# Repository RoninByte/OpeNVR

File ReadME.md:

BOARD STATUS: In Production

Photo's of the PCB;

Features:

M-Key M.2 PCIe Gen 3 X2 Slot

E-Key M.2 PCIe Gen 3 X1 Slot

2x 2.5GBe Ethernet Ports (Realtek's RTL8125BG-CG)

4x Molex Mini-Fit Jr for powering upto 3.5" Sata drives

5v Fan header for the built in fan on the Lattepanda MU

12v Fan Header for a system fan

HDMI 2.1

2x USB 3.2 Gen 2

2x USB 2.0

DDR4 SO-DIMM Slot for Lattepanda MU (Many options to choose from)

Uses Nano-ITX Standard

20v USB-C PD Input.

Dual Bios to switch between MU Bios and Your own Custom Bios

6x Sata Ports (ASM1166)

* 2 Sata ports will remain unpopulated however they will be connected to the IC incase you want to add more ports

Sata Ports LED (Once again optional)

Any Suggestions Just Open an Issue and i'll take a look

Credits:

EShark 

WifiCable for improvements and fixes

Lattepanda Team For Lattepanda MU Lite Kit

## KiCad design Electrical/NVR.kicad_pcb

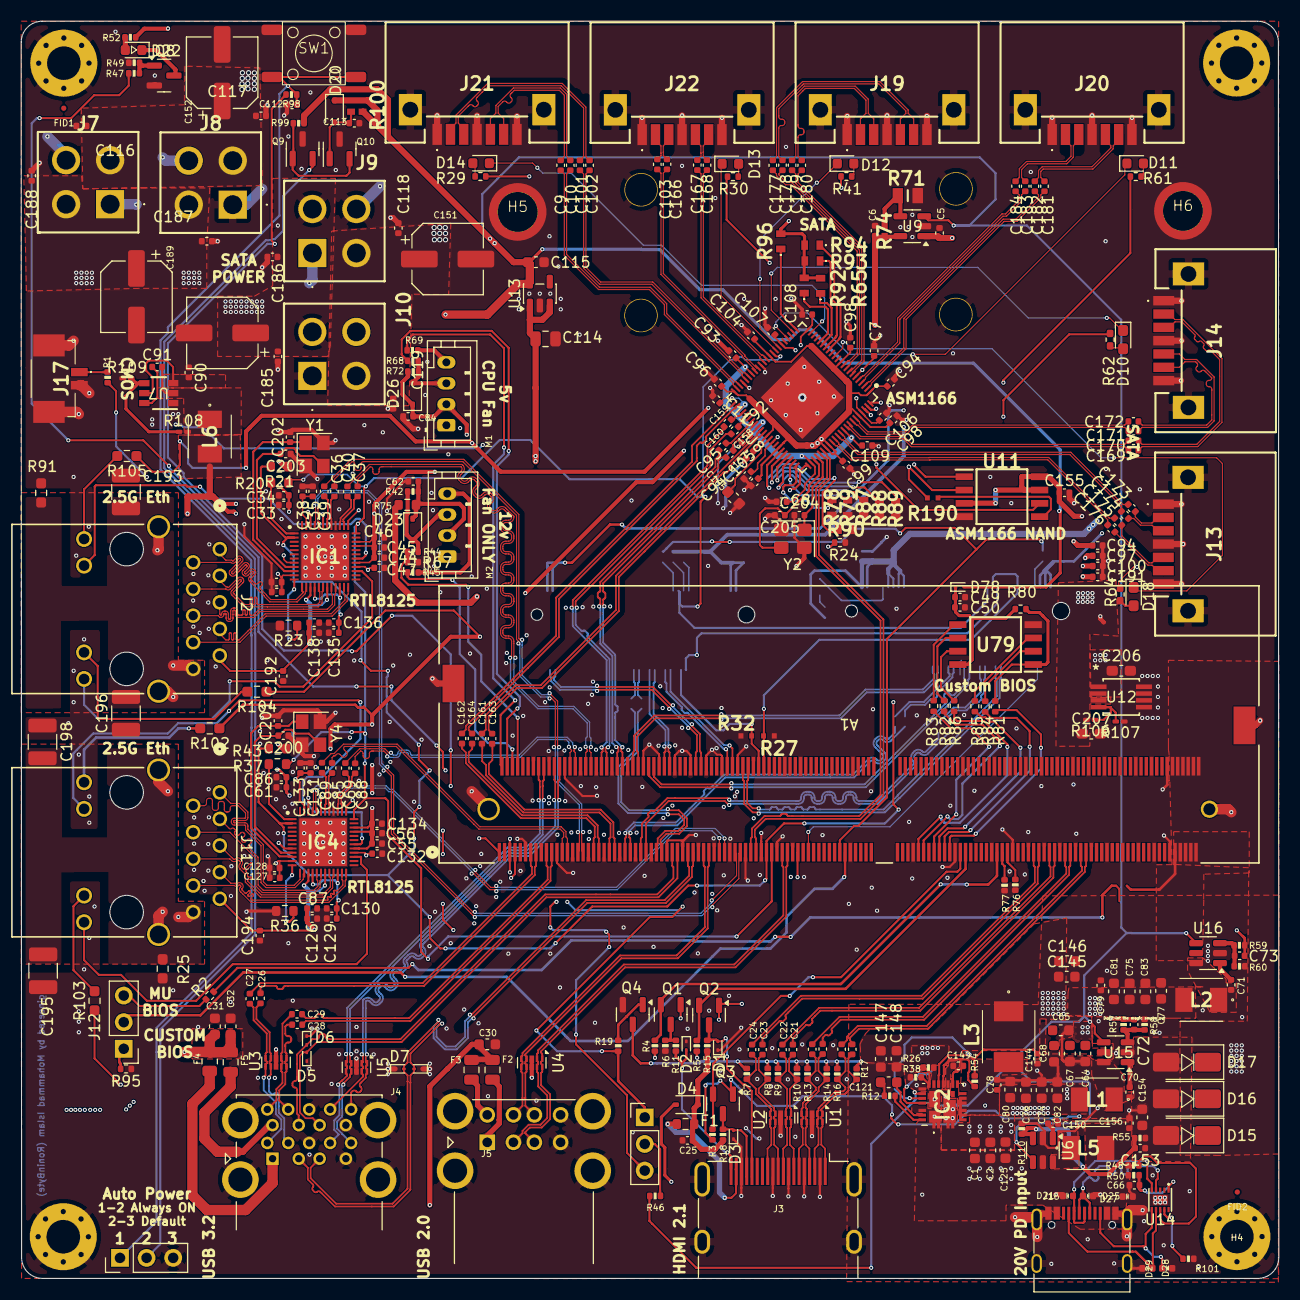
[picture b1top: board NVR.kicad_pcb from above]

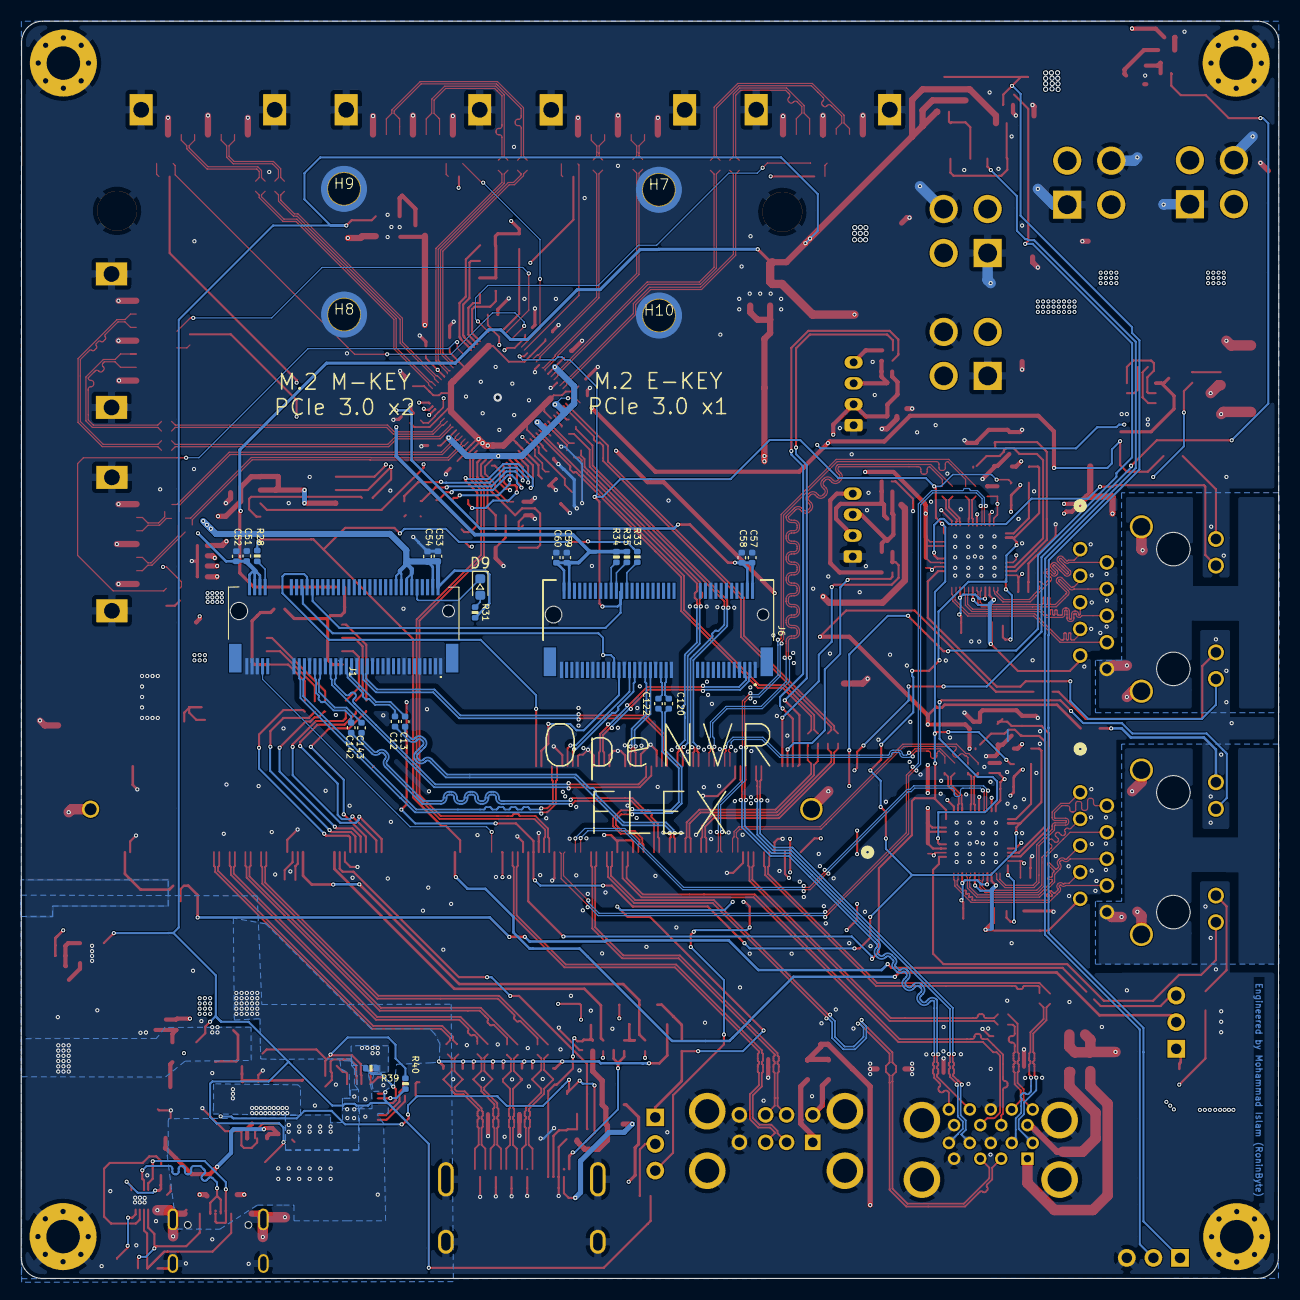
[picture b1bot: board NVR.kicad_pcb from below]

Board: 4 copper layers, 120.0 x 120.0 mm, 400 parts (28 on the bottom side), 317 nets.

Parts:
A1: TE Connectivity 2309413-1 DDR4 SODIMM H9.2mm; CONN260_2309413-1_TEC
C1, C2, C64, C65, C67, C68, C121: 22uF/50V; C_0603_1608Metric
C5, C6, C66, C112: 1uF/16V; C_0402_1005Metric
C7, C8, C11, C17, C18, C19, C20, C21, C22, C23, C24, C25, C26, C27, C28, C29, C52, C54, C58, C60, C62, C70, C71, C78, C79, C84, C91, C92, C93, C94#3, C106, C107, C108, C109, C116, C117, C118, C119, C150, C156, C185, C186, C187, C188: 100nF/50V; C_0402_1005Metric
C9, C103, C166, C167, C168, C169, C170, C171, C172, C173, C174, C175, C176, C177, C178, C179, C180, C181, C182, C183, C184: 10nF/20V; C_0402_1005Metric
C10, C101, C102: 10nF; C_0402_1005Metric
C12, C13, C120, C122, C142, C143: 220nF/50V; C_0402_1005Metric
C30, C31, C32, C74, C75, C76, C77, C80, C81, C82, C83: 22uF/10V; C_0603_1608Metric
C33, C34, C35, C36, C37, C38, C39, C40, C41, C42, C44, C45, C46, C47, C55, C56, C61, C69, C85, C86, C88, C89, C134, C135, C136, C137, C138, C192, C194: 100nF/50v; C_0402_1005Metric
C49: 22uF/6.3V; C_0402_1005Metric
C50: 0.1uF/16V; C_0402_1005Metric
C51, C53, C57, C59, C94, C94#2, C95, C96, C97, C98#2, C99, C100, C104, C113, C127, C128, C129, C130, C131, C133, C191: 10uF/10V; C_0402_1005Metric
C72, C73, C153: 12pF/50V; C_0402_1005Metric
C87, C98, C105, C126, C132: C; C_0402_1005Metric
C90: 10uF/50V; C_0402_1005Metric
C114: 10uF/50V; C_0805_2012Metric
C115: 10u/F10V; C_0603_1608Metric
C125: 100nF/50V; C_0603_1608Metric
C144: 1uF/25V; C_0402_1005Metric
C145, C146, C147, C148: 47uF; C_0603_1608Metric
C149: 4.7uF/25V; C_0402_1005Metric
C151, C152: 220uF/50V; CP_Elec_6.3x7.7
C154: 22uF/25V; C_0603_1608Metric
C155: 100uF/6.3V; C_0402_1005Metric
C157, C158, C159, C160, C161, C162, C163, C164: 220nF/10V; C_0402_1005Metric
C165: 4.7uF/1%; C_0603_1608Metric
C189, C190: 100uF/25V; CP_Elec_6.3x7.7
C193, C195, C196, C198: 2.2nF/2kv; C_1210_3225Metric_Pad1.33x2.70mm_HandSolder
C200, C201, C202, C203, C204, C205: 22pF/20V; C_0402_1005Metric
C206, C207: 2.2uF/25V; C_0603_1608Metric_Pad1.08x0.95mm_HandSolder
D1, D2, D3, D5, D6, D7, D8: ESD5V0B03; D_SOD-923
D4, D20, D23, D26: 1N5819WS; D_SOD-323
D9, D11, D12, D13, D14, D22: LED_G; LED_0603_1608Metric
D10, D18: LED_G; LED_0603_1608Metric_Pad1.05x0.95mm_HandSolder
D15, D16, D17: SS54; D_SMA
D21, D25: ESD5V0B03; D_0402_1005Metric
D27, D28, D29: PESD24VS1UL-N; D_0402_1005Metric
D78: D_Schottky; D_SOD-923
F1: 6V/50mA; R_0603_1608Metric
F2, F3: 6V/1A; Fuse_0805_2012Metric
F4: 6V/2A; R_0805_2012Metric
F5: 6V/2A; Fuse_0805_2012Metric
FID1, FID2: Fiducial; Fiducial_0.5mm_Mask1mm
H1, H2, H3, H4: MountingHole_Pad; MountingHole_3.2mm_M3_Pad_Via
H5, H6: MountingHole_Pad; MountingHole_3mm_M2_Pad_TopOnly
H7, H8, H9, H10: MountingHole_M2.0; MountingHole_3mm_M2_Pad_TopOnly
IC1, IC4: RTL8125BG-CG; QFN40P600X600X100-49N
IC2: SiC437AED-T1-GE3; SIC437DEDT1GE3
J1: Bus_M.2_Socket_M; PCIe_M.2_Connectors_P=0.5mm_H=4.2mm_KeyM
J2, J11: ARJM11A1-805-AB-EW2; ARJM11A1-805-AB-EW2_ABR
J3: HDMI_A; HDMI_A_Molex_208658-1001_Horizontal
J4: USB3_A_Stacked; USB3_A_Molex_48406-0001_Horizontal_Stacked
J5: USB_A_Stacked; USB_A_CUI_UJ2-ADH-TH_Horizontal_Stacked
J6: Bus_M.2_Socket_E; PCIe_M.2_Connectors_P=0.5mm_H=4.2mm_KeyE
J7, J8, J9, J10: 87427-0442; 874270442
J12, J15: Conn_01x03_Pin; PinHeader_1x03_P2.54mm_Vertical
J13, J14, J19, J20, J21, J22: SATA-A-PL-SMT-K; SATAAPLSMTK
J16: USB_C_Receptacle_USB2.0; USB_C_Receptacle_G-Switch_GT-USB-7010ASV
J17: 53261-0271; 532610271
JP1: Jumper_3_Bridged12; PinHeader_1x03_P2.54mm_Vertical
L1, L2, L5, L6: 2.2uH/4.3A; SPM4010-4020
L3: 1.5uH/14A; ETQ-P3M_KVP
M1, M2: Fan_4pin; JST_PH_B4B-PH-K_1x04_P2.00mm_Vertical
Q1, Q8, Q9, Q10: 2N7002; SOT-23
Q2, Q3, Q4: 2SK3018; SOT-23
R1, R11, R47, R50: 1K/1%; R_0402_1005Metric
R2, R34, R35, R48, R49, R54, R58, R60, R95, R110: 10K/1%; R_0402_1005Metric
R3, R5, R12, R15, R18, R19, R29, R30, R31, R41, R52, R61: 2.2K/1%; R_0402_1005Metric
R4: 1M/1%; R_0402_1005Metric
R6, R44, R67, R68: 21.5K/1%; R_0402_1005Metric
R7, R8, R9, R10, R13, R14, R16, R17: 470R/1%; R_0402_1005Metric
R20, R37: 1K/1%; R_0603_1608Metric
R21, R43: 4.7K/1%; R_0603_1608Metric
R23, R36: 2.49K/1%; R_0603_1608Metric
R24: RC0402FR-075KL; R_0402_1005Metric
R25, R91: 1M/1%; R_0603_1608Metric_Pad0.98x0.95mm_HandSolder
R26: 1.0K/1%; R_0402_1005Metric
R27, R32, R190: ERA-2AEB3321X; ERA2AED122X
R28, R33: 0R/1%; R_0402_1005Metric
R38: 19.1K/1%; R_0402_1005Metric
R39: 200K/1%; R_0402_1005Metric
R40: 499K/1%; R_0402_1005Metric
R42, R72: 4.7K/1%; R_0402_1005Metric
R45, R46, R69, R98: 100R/1%; R_0402_1005Metric
R55: 240K/1%; R_0402_1005Metric
R57: 75K/1%; R_0402_1005Metric
R59: 45K/1%; R_0402_1005Metric
R62, R64: 2.2K/1%; R_0402_1005Metric_Pad0.72x0.64mm_HandSolder
R65, R78, R79, R87, R88, R89, R90, R92, R93, R94, R96: ERA-3AED162V; ERA3AEB101V
R71: CPF0805B25KE1; RESC2012X65N
R74: CRCW040250K0FKED; RESC1005X40N
R75: 0R/1%; R_0603_1608Metric
R76, R77, R99: 100K/1%; R_0402_1005Metric
R80, R101: 120K/1%; R_0402_1005Metric
R81: 0R; R_0402_1005Metric
R82, R83, R84, R85, R86: 15R/1%; R_0402_1005Metric
R100: RC0402FR-071ML; RESC1005X40N
R102, R103, R104, R105: 1k/1%; R_0603_1608Metric_Pad0.98x0.95mm_HandSolder
R106: 3.16K/1%; R_0201_0603Metric_Pad0.64x0.40mm_HandSolder
R107, R109: 10.1K/1%; R_0201_0603Metric_Pad0.64x0.40mm_HandSolder
R108: 2.37K/1%; R_0201_0603Metric_Pad0.64x0.40mm_HandSolder
SW1: SW_Push; SW_Push_6x6x6
U1, U2: TPAZ1023-04F; Diodes_UDFN-10_1.0x2.5mm_P0.5mm
U3, U4, U5: ULC0524P; Diodes_UDFN-10_1.0x2.5mm_P0.5mm
U6, U15, U16: SY8253ADC; TSOT-23-6
U7: TPS562201DDCR; DDC0006A_N
U8: ASM1166; QFN-88_L10.0-W10.0-P0.40-BL-EP5.6
U9: SOT-23-5
U11, U79: W25Q128JVSIQ; SOIC127P790X216-8N
U12: ADP1715ARMZ-R7; RM_8_ADI
U13: NCP718xSN300; SOT-23-5
U14: CH224Q_C46061833; DFN-10_L2.0-W2.0-P0.40-BL-EP
Y1, Y2, Y4: 25MHz; Crystal_SMD_3225-4Pin_3.2x2.5mm

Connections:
5V_HDMI_VCC: C25.1, D4.1 (K), F1.1, R15.1, R18.1
+0V9: C35.2, C38.2, C41.2, C42.2, C47.2, C127.2, C128.2, C129.1, C130.1, C131.2, C132.2, C133.2, C135.1, C136.1, IC1.8 (DVDD09_1), IC1.11 (AVDD09_1), IC1.16 (AVDD09_2), IC1.22 (AVDD09_3), IC1.28 (DVDD09_2), IC1.37 (EVDD09), IC1.47 (DVDD09_3), IC4.8 (DVDD09_1), IC4.11 (AVDD09_1), IC4.16 (AVDD09_2), IC4.22 (AVDD09_3), IC4.28 (DVDD09_2), IC4.37 (EVDD09), IC4.47 (DVDD09_3), L6.2
+1V0: C94.2, C94#2.2, C94#3.2, C95.2, C96.2, C97.2, C98.2, C98#2.2, C99.2, C100.2, C104.2, C191.2, C207.1, R106.2, U8.1 (VDD105), U8.11 (VDD105), U8.32 (VDD105), U8.44 (VDD105), U8.50 (VDD105), U8.56 (VDD105), U8.60 (VDD105), U8.73 (VDD105), U8.74 (VDD105), U8.84 (VDD105), U12.3 (OUT)
+2V5: C6.1, C7.2, C8.2, C11.2, C92.2, C93.1, C109.2, R74.1, U8.6 (VCC25), U8.38 (VCC25), U8.47 (VCC25P), U8.53 (VCC25P), U8.68 (VCC25CK), U8.79 (VCC25), U9.5 (VOUT)
+3V3: C5.2, C33.2, C34.2, C44.2, C45.2, C46.2, C51.2, C52.2, C53.2, C54.2, C55.2, C56.2, C57.2, C58.2, C59.2, C60.2, C61.2, C73.1, C75.2, C77.2, C79.1, C81.2, C83.2, C86.2, C87.1, C105.2, C106.2, C107.2, C108.2, C126.1, C134.2, C137.1, C138.1, C155.1, C192.2, C194.2, C206.1, IC1.15 (AVDD33_1), IC1.19 (AVDD33_2), IC1.29 (DVDD33_1), IC1.33 (AVDD33_3), IC1.34 (AVDD33_XTAL), IC1.43 (EVDD33), IC1.46 (DVDD33_2), IC4.15 (AVDD33_1), IC4.19 (AVDD33_2), IC4.29 (DVDD33_1), IC4.33 (AVDD33_3), IC4.34 (AVDD33_XTAL), IC4.43 (EVDD33), IC4.46 (DVDD33_2), J1.2 (3.3V), J1.4 (3.3V), J1.12 (3.3V), J1.14 (3.3V), J1.16 (3.3V), J1.18 (3.3V), J1.70 (3.3V), J1.72 (3.3V), J1.74 (3.3V), J2.9 (VCC), J6.2 (3.3V), J6.4 (3.3V), J6.72 (3.3V), J6.74 (3.3V), J11.9 (VCC), L2.2, Q1.1 (G), Q2.1 (G), Q3.1 (G), R3.1, R4.1, R5.1, R29.2, R30.2, R31.2, R34.2, R35.1, R41.2, R52.2, R59.2, R61.2, R62.2, R64.2, R65.2, R92.2, R93.2, R94.2, R96.2, R102.1, R103.1, R104.1, R105.1, U8.22 (VCC33), U8.28 (VCC33), U8.58 (VCC33), U8.85 (VCC33), U9.1 (VIN), U11.3 (IO2), U11.7 (IO3), U11.8 (VCC), U12.1 (EN), U12.2 (IN)
+3V3_SB: C115.1, D20.1 (K), D78.2 (A), IC2.19 (EN), R21.1, R43.1, R46.2, R99.2, R100.2, U6.4 (EN), U9.3 (EN), U13.5 (OUT), U15.4 (EN), U16.4 (EN)
+5V: C30.2, C31.2, C32.2, C72.1, C74.2, C76.2, C78.1, C80.2, C82.2, C84.1, C90.2, C185.1, C186.1, C187.1, C188.1, C189.1, C190.1, D4.2 (A), D26.1 (K), F2.1, F3.1, F4.1, F5.1, J7.2, J8.2, J9.2, J10.2, L1.2, M1.2 (+), R57.2, R72.1, U7.3 (VIN), U7.5 (EN)
+12V: C116.1, C117.1, C118.1, C119.1, C145.1, C146.1, C147.1, C148.1, C151.1, C152.1, IC2.18 (VOUT), J7.3, J8.3, J9.3, J10.3, L3.1, R38.2, R75.2
+15V: C153.1, C154.2, C156.1, D15.2 (A), D16.2 (A), D17.2 (A), L5.2, R55.2
+20V: C1.1, C2.1, C114.1, C125.1, D27.1 (K), IC2.1 (VIN_1), IC2.2 (VIN_2), IC2.22 (VIN_3), IC2.26 (VIN_4), J16.A4 (VBUS), J16.A9 (VBUS), J16.B4 (VBUS), J16.B9 (VBUS), R48.1, R50.1, U6.5 (VIN), U13.1 (IN), U13.3 (EN)
+BATT: A1.115 (VBAT), R1.1
/BIOS/SPI-CS: A1.165 (~SPI_CS), R81.1
/BIOS/SPI-IO0: A1.159 (SPI_MOSI/SPI_IO0), R83.1
/BIOS/SPI-IO1: A1.163 (SPI_MISO/SPI_IO1), R84.1
/BIOS/SPI-IO2: A1.161 (SPI_IO2), R85.1
/BIOS/SPI-IO3: A1.153 (SPI_IO3), R86.1
/BIOS/SPI_CLK: A1.155 (SPI_CLK), R82.1
/Fan_Temp/FAN_1_PWM: A1.2 (FAN1_PWM), R69.1
/Fan_Temp/FAN_1_TAC: A1.4 (FAN1_TAC), R68.2
/Fan_Temp/FAN_2_PWM: A1.6 (FAN2_PWM), R45.1
/Fan_Temp/FAN_2_TAC: A1.8 (FAN2_TAC), R44.2, R67.1
/Gigabit Ethernet/GbE_PCIe_0_RX+: A1.28 (HSIO2_RX+), C88.1
/Gigabit Ethernet/GbE_PCIe_0_RX-: A1.30 (HSIO2_RX-), C69.1
/Gigabit Ethernet/GbE_PCIe_0_TX+: A1.25 (HSIO2_TX+), C85.1
/Gigabit Ethernet/GbE_PCIe_0_TX-: A1.27 (HSIO2_TX-), C89.1
/Gigabit Ethernet/GbE_PCIe_1_RX+: A1.34 (HSIO3_RX+), C37.1
/Gigabit Ethernet/GbE_PCIe_1_RX-: A1.36 (HSIO3_RX-), C40.1
/Gigabit Ethernet/GbE_PCIe_1_TX+: A1.31 (HSIO3_TX+), C36.1
/Gigabit Ethernet/GbE_PCIe_1_TX-: A1.33 (HSIO3_TX-), C39.1
/Gigabit Ethernet/GbE_PCIe_CLK0+: A1.85 (REFCLK0+), IC4.44 (REFCLK_P)
/Gigabit Ethernet/GbE_PCIe_CLK0-: A1.87 (REFCLK0-), IC4.45 (REFCLK_N)
/Gigabit Ethernet/HSI_0+: C36.2, IC1.41 (HSIP)
/Gigabit Ethernet/HSI_0-: C39.2, IC1.42 (HSIN)
/Gigabit Ethernet/HSI_1+: C85.2, IC4.41 (HSIP)
/Gigabit Ethernet/HSI_1-: C89.2, IC4.42 (HSIN)
/Gigabit Ethernet/HSO_0+: C37.2, IC1.38 (HSOP)
/Gigabit Ethernet/HSO_0-: C40.2, IC1.39 (HSON)
/Gigabit Ethernet/HSO_1+: C88.2, IC4.38 (HSOP)
/Gigabit Ethernet/HSO_1-: C69.2, IC4.39 (HSON)
/Gigabit Ethernet/LED0: IC4.30 (LED0/EEDI/SPISI/SDA), J11.12 (CATHODE)
/Gigabit Ethernet/LED0_ETH1: IC1.30 (LED0/EEDI/SPISI/SDA), J2.12 (CATHODE)
/Gigabit Ethernet/LED1: IC4.27 (LED1/EESK/SPISCK), J11.14 (CATHODE)
/Gigabit Ethernet/LED1_ETH1: IC1.27 (LED1/EESK/SPISCK), J2.14 (CATHODE)
/Gigabit Ethernet/MDI0+: IC1.13 (MDIP0), J2.1 (TD1+)
/Gigabit Ethernet/MDI0-: IC1.14 (MDIN0), J2.2 (TD1-)
/Gigabit Ethernet/MDI1+: IC1.17 (MDIP1), J2.3 (TD2+)
/Gigabit Ethernet/MDI1-: IC1.18 (MDIN1), J2.4 (TD2-)
/Gigabit Ethernet/MDI2+: IC1.20 (MDIP2), J2.5 (TD3+)
/Gigabit Ethernet/MDI2-: IC1.21 (MDIN2), J2.6 (TD3-)
/Gigabit Ethernet/MDI3+: IC1.23 (MDIP3), J2.7 (TD4+)
/Gigabit Ethernet/MDI3-: IC1.24 (MDIN3), J2.8 (TD4-)
/Gigabit Ethernet/MDI_0+: IC4.13 (MDIP0), J11.1 (TD1+)
/Gigabit Ethernet/MDI_0-: IC4.14 (MDIN0), J11.2 (TD1-)
/Gigabit Ethernet/MDI_1+: IC4.17 (MDIP1), J11.3 (TD2+)
/Gigabit Ethernet/MDI_1-: IC4.18 (MDIN1), J11.4 (TD2-)
/Gigabit Ethernet/MDI_2+: IC4.20 (MDIP2), J11.5 (TD3+)
/Gigabit Ethernet/MDI_2-: IC4.21 (MDIN2), J11.6 (TD3-)
/Gigabit Ethernet/MDI_3+: IC4.23 (MDIP3), J11.7 (TD4+)
/Gigabit Ethernet/MDI_3-: IC4.24 (MDIN3), J11.8 (TD4-)
/Gigabit Ethernet/~WAKE: IC1.2 (LANWAKEB), IC4.2 (LANWAKEB), R21.2, R43.2
/HDMI/DDC_SCL: D1.2 (A2), J3.15 (SCL), Q2.3 (D), R15.2
/HDMI/DDC_SDA: D3.2 (A2), J3.16 (SDA), Q3.3 (D), R18.2
/HDMI/DDI_B_DDC_SCL: A1.171 (DDIB_DDC_SCL), Q2.2 (S), R5.2
/HDMI/DDI_B_DDC_SDA: A1.169 (DDIB_DDC_SDA), Q3.2 (S), R3.2
/HDMI/DDI_B_HPD: A1.183 (DDIB_HPD), Q1.2 (S), R4.2
/HDMI/DDI_B_TX0+: A1.217 (DDIB_TX0+), C17.1
/HDMI/DDI_B_TX0-: A1.215 (DDIB_TX0-), C18.1
/HDMI/DDI_B_TX1+: A1.211 (DDIB_TX1+), C19.1
/HDMI/DDI_B_TX1-: A1.209 (DDIB_TX1-), C20.1
/HDMI/DDI_B_TX2+: A1.205 (DDIB_TX2+), C21.1
/HDMI/DDI_B_TX2-: A1.203 (DDIB_TX2-), C22.1
/HDMI/DDI_B_TX3+: A1.199 (DDIB_TX3+), C23.1
/HDMI/DDI_B_TX3-: A1.197 (DDIB_TX3-), C24.1
/HDMI/HPD: D2.2 (A2), J3.19 (HPD), R11.2
/HDMI/TMDS_CK+: C23.2, J3.10 (CK+), R8.1, U2.4, U2.7 (NC)
/HDMI/TMDS_CK-: C24.2, J3.12 (CK-), R7.1, U2.5, U2.6 (NC)
/HDMI/TMDS_D0+: C21.2, J3.7 (D0+), R10.1, U2.1, U2.10 (NC)
/HDMI/TMDS_D0-: C22.2, J3.9 (D0-), R9.1, U2.2, U2.9 (NC)
/HDMI/TMDS_D1+: C19.2, J3.4 (D1+), R14.1, U1.4, U1.7 (NC)
/HDMI/TMDS_D1-: C20.2, J3.6 (D1-), R13.1, U1.5, U1.6 (NC)
/HDMI/TMDS_D2+: C17.2, J3.1 (D2+), R17.1, U1.1, U1.10 (NC)
/HDMI/TMDS_D2-: C18.2, J3.3 (D2-), R16.1, U1.2, U1.9 (NC)
/LattePanda Module/HSIO_0_TX+: A1.13 (HSIO0_TX+), C27.1
/LattePanda Module/HSIO_0_TX-: A1.15 (HSIO0_TX-), C26.1
/LattePanda Module/HSIO_1_TX+: A1.19 (HSIO1_TX+), C29.1
/LattePanda Module/HSIO_1_TX-: A1.21 (HSIO1_TX-), C28.1
/LattePanda Module/HSIO_6_RX+: A1.64 (HSIO6_RX+), J6.41 (PERp0)
/LattePanda Module/HSIO_6_RX-: A1.66 (HSIO6_RX-), J6.43 (PERn0)
/LattePanda Module/HSIO_6_TX+: A1.61 (HSIO6_TX+), C120.1
/LattePanda Module/HSIO_6_TX-: A1.63 (HSIO6_TX-), C122.1
/LattePanda Module/HSIO_8_RX+: A1.40 (HSIO8_RX+), C159.2
/LattePanda Module/HSIO_8_RX-: A1.42 (HSIO8_RX-), C158.2
/LattePanda Module/HSIO_8_TX+: A1.37 (HSIO8_TX+), C162.1, C162.2
/LattePanda Module/HSIO_8_TX-: A1.39 (HSIO8_TX-), C164.1, C164.2
/LattePanda Module/HSIO_9_RX+: A1.46 (HSIO9_RX+), C160.2
/LattePanda Module/HSIO_9_RX-: A1.48 (HSIO9_RX-), C157.2
/LattePanda Module/HSIO_9_TX+: A1.43 (HSIO9_TX+), C161.1, C161.2
/LattePanda Module/HSIO_9_TX-: A1.45 (HSIO9_TX-), C163.1, C163.2
/LattePanda Module/HSIO_10_RX+: A1.52 (HSIO10_RX+), J1.29 (PERn1)
/LattePanda Module/HSIO_10_RX-: A1.54 (HSIO10_RX-), J1.31 (PERp1)
/LattePanda Module/HSIO_10_TX+: A1.49 (HSIO10_TX+), C13.1
/LattePanda Module/HSIO_10_TX-: A1.51 (HSIO10_TX-), C12.1
/LattePanda Module/HSIO_11_RX+: A1.58 (HSIO11_RX+), J1.43 (PERp0/SATA-B-)
/LattePanda Module/HSIO_11_RX-: A1.60 (HSIO11_RX-), J1.41 (PERn0/SATA-B+)
/LattePanda Module/HSIO_11_TX+: A1.55 (HSIO11_TX+), C143.1
/LattePanda Module/HSIO_11_TX-: A1.57 (HSIO11_TX-), C142.1
/LattePanda Module/REFCLK2+: A1.97 (REFCLK2+), U8.71 (PECLKP)
/LattePanda Module/REFCLK2-: A1.99 (REFCLK2-), U8.72 (PECLKN)
/LattePanda Module/REFCLK3+: A1.88 (REFCLK3+), J6.47 (REFCLKp0)
/LattePanda Module/REFCLK3-: A1.90 (REFCLK3-), J6.49 (REFCLKn0)
/LattePanda Module/REFCLK4+: A1.94 (REFCLK4+), J1.55 (REFCLKp)
/LattePanda Module/REFCLK4-: A1.96 (REFCLK4-), J1.53 (REFCLKn)
/LattePanda Module/SATAXPCIE_0: A1.119 (GPP_E0), J1.69 (PEDET)
/LattePanda Module/SLS_S3: A1.7 (SLS_S3), JP1.3 (B)
/LattePanda Module/SUSCLK_WIFI: A1.131 (SUSCLK), R28.2, R33.2
/LattePanda Module/USB_2_P7+: A1.76 (USB2_P7+), J6.3 (USB_D+)
/LattePanda Module/USB_2_P7-: A1.78 (USB2_P7-), J6.5 (USB_D-)
/LattePanda Module/~CLKREQE: A1.100 (~CLKREQ3), J6.53 (~CLKREQ0), R32.2
/LattePanda Module/~CLKREQM: A1.102 (~CLKREQ4), J1.52 (~CLKREQ), R27.2
/LattePanda Module/~PWR_SW: A1.1 (~PWRBTN), R98.2
/M.2 E&M Key/CON_PCIE_TX_0+: C13.2, J1.35 (PETn1)
/M.2 E&M Key/CON_PCIE_TX_0-: C12.2, J1.37 (PETp1)
/M.2 E&M Key/CON_PCIE_TX_1+: C143.2, J1.47 (PETn0/SATA-A-)
/M.2 E&M Key/CON_PCIE_TX_1-: C142.2, J1.49 (PETp0/SATA-A+)
/M.2 E&M Key/CON_PCIE_TX_2+: C120.2, J6.35 (PETp0)
/M.2 E&M Key/CON_PCIE_TX_2-: C122.2, J6.37 (PETn0)
/PCIe to SATA/LED_0: D14.1 (K), U8.21 (LED_S0)
/PCIe to SATA/LED_1: D13.1 (K), U8.30 (LED_S1)
/PCIe to SATA/LED_2: D12.1 (K), U8.29 (LED_S2)
/PCIe to SATA/LED_3: D11.1 (K), U8.26 (LED_S3)
/PCIe to SATA/LED_4: D10.1 (K), U8.24 (LED_S4)
/PCIe to SATA/LED_5: D18.1 (K), U8.13 (LED_S5)
/PCIe to SATA/RX_N_0: C10.2, U8.42 (SRXN0)
/PCIe to SATA/RX_N_1: C167.2, U8.34 (SRXN1)
/PCIe to SATA/RX_N_2: C178.2, U8.9 (SRXN2)
/PCIe to SATA/RX_N_3: C182.2, U8.3 (SRXN3)
/PCIe to SATA/RX_N_4: C171.2, U8.82 (SRXN4)
/PCIe to SATA/RX_N_5: C175.2, U8.76 (SRXN5)
/PCIe to SATA/RX_P_0: C9.2, U8.43 (SRXP0)
/PCIe to SATA/RX_P_1: C168.2, U8.33 (SRXP1)
/PCIe to SATA/RX_P_2: C177.2, U8.10 (SRXP2)
/PCIe to SATA/RX_P_3: C181.2, U8.2 (SRXP3)
/PCIe to SATA/RX_P_4: C172.2, U8.83 (SRXP4)
/PCIe to SATA/RX_P_5: C176.2, U8.75 (SRXP5)
/PCIe to SATA/TX_N_0: C101.2, U8.40 (STXN0)
/PCIe to SATA/TX_N_1: C166.2, U8.36 (STXN1)
/PCIe to SATA/TX_N_2: C179.2, U8.8 (STXN2)
/PCIe to SATA/TX_N_3: C183.2, U8.4 (STXN3)
/PCIe to SATA/TX_N_4: C170.2, U8.81 (STXN4)
/PCIe to SATA/TX_N_5: C174.2, U8.77 (STXN5)
/PCIe to SATA/TX_P_0: C102.2, U8.39 (STXP0)
/PCIe to SATA/TX_P_1: C103.2, U8.37 (STXP1)
/PCIe to SATA/TX_P_2: C180.2, U8.7 (STXP2)
/PCIe to SATA/TX_P_3: C184.2, U8.5 (STXP3)
/PCIe to SATA/TX_P_4: C169.2, U8.80 (STXP4)
/PCIe to SATA/TX_P_5: C173.2, U8.78 (STXP5)
/PSU/CC1: D28.1 (K), J16.A5 (CC1), U14.7 (CC1)
/PSU/CC2: D29.1 (K), J16.B5 (CC2), U14.6 (CC2)
/PSU/PWR_C_D+: D25.2 (A2), J16.A6 (D+), J16.B6 (D+), U14.4 (DP)
/PSU/PWR_C_D-: D21.2 (A2), J16.A7 (D-), J16.B7 (D-), U14.5 (DM)
/USB2.0&USB3.0/CON_USB1_D_N: A1.109 (USB2_P5-), J5.2 (D1-), U4.2, U4.9 (NC)
/USB2.0&USB3.0/CON_USB1_D_P: A1.111 (USB2_P5+), J5.3 (D1+), U4.1, U4.10 (NC)
/USB2.0&USB3.0/CON_USB2_D_N: A1.79 (USB2_P3-), J5.6 (D2-), U4.5, U4.6 (NC)
/USB2.0&USB3.0/CON_USB2_D_P: A1.81 (USB2_P3+), J5.7 (D2+), U4.4, U4.7 (NC)
/USB2.0&USB3.0/CON_USB3_D_N: A1.73 (USB2_P2-), D8.2 (A2), J4.2 (D1-)
/USB2.0&USB3.0/CON_USB3_D_P: A1.75 (USB2_P2+), D7.2 (A2), J4.3 (D1+)
/USB2.0&USB3.0/CON_USB3_SSRX_N: A1.18 (HSIO0_RX-), J4.5 (SSRX1-), U5.4, U5.7 (NC)
/USB2.0&USB3.0/CON_USB3_SSRX_P: A1.16 (HSIO0_RX+), J4.6 (SSRX1+), U5.5, U5.6 (NC)
/USB2.0&USB3.0/CON_USB3_SSTX_N: C26.2, J4.8 (SSTX1-), U3.4, U3.7 (NC)
/USB2.0&USB3.0/CON_USB3_SSTX_P: C27.2, J4.9 (SSTX1+), U3.5, U3.6 (NC)
/USB2.0&USB3.0/CON_USB4_D_N: A1.67 (USB2_P1-), D6.2 (A2), J4.11 (D2-)
/USB2.0&USB3.0/CON_USB4_D_P: A1.69 (USB2_P1+), D5.2 (A2), J4.12 (D2+)
/USB2.0&USB3.0/CON_USB4_SSRX_N: A1.24 (HSIO1_RX-), J4.14 (SSRX2-), U5.1, U5.10 (NC)
/USB2.0&USB3.0/CON_USB4_SSRX_P: A1.22 (HSIO1_RX+), J4.15 (SSRX2+), U5.2, U5.9 (NC)
/USB2.0&USB3.0/CON_USB4_SSTX_N: C28.2, J4.17 (SSTX2-), U3.1, U3.10 (NC)
/USB2.0&USB3.0/CON_USB4_SSTX_P: C29.2, J4.18 (SSTX2+), U3.2, U3.9 (NC)
/~PLT_RST: IC1.36 (PERSTB), IC4.36 (PERSTB), J1.50 (~PERST), J6.52 (~PERST0), R20.1, R37.1
/~PWR_LED/~PSON: A1.5 (SLS_S0), JP1.1 (A), R19.1, R47.1
/~WAKE: A1.103 (~WAKE), J1.54 (~PEWAKE), J6.55 (~PEWAKE0)
ETH_GND: C193.2, C196.2, J2.10 (GND), R91.2
ETH_GND_2: C195.2, C198.2, J11.10 (GND), R25.2
GND: A1.11 (GND), A1.14 (GND), A1.17 (GND), A1.20 (GND), A1.23 (GND), A1.26 (GND), A1.29 (GND), A1.32 (GND), A1.35 (GND), A1.38 (GND), A1.41 (GND), A1.44 (GND), A1.47 (GND), A1.50 (GND), A1.53 (GND), A1.56 (GND), A1.59 (GND), A1.62 (GND), A1.65 (GND), A1.68 (GND), A1.71 (GND), A1.74 (GND), A1.77 (GND), A1.80 (GND), A1.83 (GND), A1.86 (GND), A1.89 (GND), A1.92 (GND), A1.95 (GND), A1.98 (GND), A1.101 (GND), A1.107 (GND), A1.110 (GND), A1.113 (GND), A1.116 (GND), A1.135 (GND), A1.136 (GND), A1.151 (GND), A1.158 (GND), A1.167 (GND), A1.170 (GND), A1.181 (GND), A1.182 (GND), A1.188 (GND), A1.189 (GND), A1.194 (GND), A1.195 (GND), A1.200 (GND), A1.201 (GND), A1.206 (GND), A1.207 (GND), A1.212 (GND), A1.213 (GND), A1.218 (GND), A1.219 (GND), A1.224 (GND), A1.225 (GND), A1.230 (GND), A1.231 (GND), A1.236 (GND), A1.237 (GND), A1.242 (GND), A1.243 (GND), A1.248 (GND), A1.249 (GND), C5.1, C6.2, C7.1, C8.1, C11.1, C25.2, C30.1, C31.1, C32.1, C33.1, C34.1, C35.1, C38.1, C41.1, C42.1, C44.1, C45.1, C46.1, C47.1, C49.2, C50.2, C51.1, C52.1, C53.1, C54.1, C55.1, C56.1, C57.1, C58.1, C59.1, C60.1, C61.1, C62.2, C64.2, C65.1, C66.2, C67.2, C68.1, C74.1, C75.1, C76.1, C77.1, C78.2, C79.2, C80.1, C81.1, C82.1, C83.1, C84.2, C86.1, C87.2, C90.1, C92.1, C93.2, C94.1, C94#2.1, C94#3.1, C95.1, C96.1, C97.1, C98.1, C98#2.1, C99.1, C100.1, C104.1, C105.1, C106.1, C107.1, C108.1, C109.1, C112.2, C113.2, C114.2, C115.2, C116.2, C117.2, C118.2, C119.2, C126.2, C127.1, C128.1, C129.2, C130.2, C131.1, C132.1, C133.1, C134.1, C135.2, C136.2, C137.2, C138.2, C144.2, C145.2, C146.2, C147.2, C148.2, C151.2, C152.2, C154.1, C155.2, C156.2, C165.1, C185.2, C186.2, C187.2, C188.2, C189.2, C190.2, C191.1, C192.1, C193.1, C194.1, C195.1, C196.1, C198.1, C200.1, C201.2, C202.2, C203.1, C204.1, C205.2, C206.2, C207.2, D1.1 (A1), D2.1 (A1), D3.1 (A1), D5.1 (A1), D6.1 (A1), D7.1 (A1), D8.1 (A1), D21.1 (A1), D25.1 (A1), D27.2 (A), D28.2 (A), D29.2 (A), H1.1 (1_1), H2.1 (1_1), H3.1 (1_1), H4.1 (1_1), H5.1 (1_1), H6.1 (1_1), H7.1 (1_1), H8.1 (1_1), H9.1 (1_1), H10.1 (1_1), IC1.40 (GND_1), IC1.49 (GND_2), IC4.40 (GND_1), IC4.49 (GND_2), J1.1 (GND), J1.3 (GND), J1.9 (GND), J1.15 (GND), J1.21 (GND), J1.27 (GND), J1.33 (GND), J1.39 (GND), J1.45 (GND), J1.51 (GND), J1.57 (GND), J1.71 (GND), J1.73 (GND), J1.75 (GND), J3.2 (D2S), J3.5 (D1S), J3.8 (D0S), J3.11 (CKS), J3.17 (GND), J3.SH, J4.4 (GND1), J4.7 (DRAIN1), J4.13 (GND2), J4.16 (DRAIN2), J4.19 (SHIELD), J5.4 (GND1), J5.8 (GND2), J5.9 (Shield), J6.1 (GND), J6.7 (GND), J6.18 (GND), J6.33 (GND), J6.39 (GND), J6.45 (GND), J6.51 (GND), J6.57 (GND), J6.63 (GND), J6.69 (GND), J6.75 (GND), J7.1, J7.4, J8.1, J8.4, J9.1, J9.4, J10.1, J10.4, J13.1 (MH1), J13.2 (MH2), J13.S1 (GND_1), J13.S4 (GND_2), J13.S7 (GND_3), J14.1 (MH1), J14.2 (MH2), J14.S1 (GND_1), J14.S4 (GND_2), J14.S7 (GND_3), J15.3, J16.A1 (GND), J16.A12 (GND), J16.B1 (GND), J16.B12 (GND), J16.S1 (SHIELD), J17.2, J17.MP1, J17.MP2, J19.1 (MH1), J19.2 (MH2), J19.S1 (GND_1), J19.S4 (GND_2), J19.S7 (GND_3), J20.1 (MH1), J20.2 (MH2), J20.S1 (GND_1), J20.S4 (GND_2), J20.S7 (GND_3), J21.1 (MH1), J21.2 (MH2), J21.S1 (GND_1), J21.S4 (GND_2), J21.S7 (GND_3), J22.1 (MH1), J22.2 (MH2), J22.S1 (GND_1), J22.S4 (GND_2), J22.S7 (GND_3), M1.1 (-), M2.1 (-), Q4.2 (S), Q8.2 (S), Q9.3 (D), Q10.3 (D), R6.2, R23.2, R24.2, R25.1, R27.1, R32.1, R36.2, R49.1, R58.1, R60.1, R67.2, R71.2, R76.2, R77.2, R78.2, R79.2, R87.2, R88.2, R89.2, R90.2, R91.1, R95.1, R101.1, R107.1, R109.1, R110.1, SW1.1, U1.3 (VSS), U1.8 (VSS), U2.3 (VSS), U2.8 (VSS), U3.3 (VSS), U3.8 (VSS), U4.3 (VSS), U4.8 (VSS), U5.3 (VSS), U5.8 (VSS), U6.2 (GND), U7.1 (GND), U8.35 (GNDA), U8.41 (GNDA), U8.89 (EP), U9.2 (GND), U11.4 (GND), U12.5 (GND), U12.6 (GND), U12.7 (GND), U12.8 (GND), U13.2 (GND), U14.11 (EP), U15.2 (GND), U16.2 (GND), U79.4 (GND), Y1.2, Y1.4, Y2.2, Y2.4, Y4.2, Y4.4
unnamed: A1.187 (TCP0_HPD), R76.1
unnamed: A1.185 (TCP1_HPD), R77.1
unnamed: A1.133 (~BIOS_SEL), J12.2
unnamed: C121.2, R12.1
unnamed: D9.2 (A), R31.1
unnamed: D9.1 (K), J1.10 (DAS/~DSS/~LED1)
unnamed: D10.2 (A), R62.1
unnamed: D11.2 (A), R61.1
unnamed: D12.2 (A), R41.1
unnamed: D13.2 (A), R30.1
unnamed: D14.2 (A), R29.1
unnamed: C64.1, C65.2, C67.1, C68.2, D15.1 (K), D16.1 (K), D17.1 (K), U15.5 (VIN), U16.5 (VIN)
unnamed: D18.2 (A), R64.1
unnamed: C113.1, D20.2 (A), Q10.1 (G), R100.1
unnamed: D22.2 (A), R52.1
unnamed: D22.1 (K), Q8.3 (D)
unnamed: D23.2 (A), M2.3 (Tacho), R42.2, R44.1
unnamed: C62.1, D23.1 (K), M2.2 (+), R42.1, R75.1
unnamed: D26.2 (A), M1.3 (Tacho), R68.1, R72.2
unnamed: C49.1, C50.1, D78.1 (K), R80.1, U79.8 (VCC)
unnamed: C202.1, IC1.10 (CKXTAL1), Y1.1
unnamed: C203.2, IC1.9 (CKXTAL2), Y1.3
unnamed: IC1.1 (ISOLATEB), R20.2
unnamed: IC1.12 (RSET), R23.1
unnamed: C121.1, IC2.23 (BOOT)
unnamed: IC2.17 (FB), R26.2, R38.1
unnamed: IC2.21 (MODE1), R39.2
unnamed: IC2.20 (MODE2), R40.2
unnamed: IC2.14 (PGOOD), R54.1
unnamed: IC2.24 (PHASE), R12.2
unnamed: IC2.5 (SW_1), IC2.6 (SW_2), IC2.7 (SW_3), IC2.8 (SW_4), IC2.9 (SW_5), IC2.30 (SW_6), L3.2
unnamed: C144.1, IC2.15 (VDD), R40.1, R54.2
unnamed: C149.1, IC2.12 (VDRV)
unnamed: C201.1, IC4.10 (CKXTAL1), Y4.1
unnamed: C200.2, IC4.9 (CKXTAL2), Y4.3
unnamed: IC4.1 (ISOLATEB), R37.2
unnamed: IC4.12 (RSET), R36.1
unnamed: J1.68 (SUSCLK), R28.1
unnamed: J2.11 (ANODE), R105.2
unnamed: J2.13 (ANODE), R104.2
unnamed: F1.2, J3.18 (+5V)
unnamed: F4.2, J4.1 (VBUS1)
unnamed: F5.2, J4.10 (VBUS2)
unnamed: F2.2, J5.1 (VBUS1)
unnamed: F3.2, J5.5 (VBUS2)
unnamed: J6.50 (SUSCLK), R33.1
unnamed: J6.56 (~W_DISABLE1), R34.1
unnamed: J6.54 (~W_DISABLE2), R35.2
unnamed: J11.11 (ANODE), R102.2
unnamed: J11.13 (ANODE), R103.2
unnamed: J12.1, R95.2
unnamed: J12.3, R2.1
unnamed: C173.1, J13.S2 (A+)
unnamed: C174.1, J13.S3 (A-)
unnamed: C176.1, J13.S6 (B+)
unnamed: C175.1, J13.S5 (B-)
unnamed: C169.1, J14.S2 (A+)
unnamed: C170.1, J14.S3 (A-)
unnamed: C172.1, J14.S6 (B+)
unnamed: C171.1, J14.S5 (B-)
unnamed: C112.1, J15.1, R98.1, SW1.2
unnamed: J15.2, Q9.2 (S)
unnamed: J17.1, R1.2
unnamed: C180.1, J19.S2 (A+)
unnamed: C179.1, J19.S3 (A-)
unnamed: C177.1, J19.S6 (B+)
unnamed: C178.1, J19.S5 (B-)
unnamed: C184.1, J20.S2 (A+)
unnamed: C183.1, J20.S3 (A-)
unnamed: C181.1, J20.S6 (B+)
unnamed: C182.1, J20.S5 (B-)
unnamed: C102.1, J21.S2 (A+)
unnamed: C101.1, J21.S3 (A-)
unnamed: C9.1, J21.S6 (B+)
unnamed: C10.1, J21.S5 (B-)
unnamed: C103.1, J22.S2 (A+)
unnamed: C166.1, J22.S3 (A-)
unnamed: C168.1, J22.S6 (B+)
unnamed: C167.1, J22.S5 (B-)
unnamed: JP1.2 (C), R46.1
unnamed: M1.4 (PWM), R69.2
unnamed: M2.4 (PWM), R45.2
unnamed: Q1.3 (D), R6.1, R11.1
unnamed: Q4.3 (D), R7.2, R8.2, R9.2, R10.2, R13.2, R14.2, R16.2, R17.2
unnamed: Q4.1 (G), R19.2
unnamed: Q8.1 (G), R47.2, R49.2
unnamed: Q9.1 (G), Q10.2 (S), R99.1
unnamed: C150.2, U6.1 (BOOST)
unnamed: C153.2, R55.1, R110.2, U6.3 (FB)
unnamed: C150.1, L5.1, U6.6 (SW)
unnamed: C91.2, L6.1, R108.2, U7.2 (SW)
unnamed: C91.1, U7.6 (VBST)
unnamed: R108.1, R109.2, U7.4 (VFB)
unnamed: R78.1, U8.66 (GPIO0)
unnamed: R79.1, U8.65 (GPIO1)
unnamed: R87.1, U8.64 (GPIO2)
unnamed: R88.1, U8.63 (GPIO3)
unnamed: R89.1, U8.62 (GPIO4)
unnamed: R90.1, U8.61 (GPIO5)
unnamed: R94.1, U8.15 (I2CS_CLK)
unnamed: R93.1, U8.16 (I2CS_DAT)
unnamed: C158.1, U8.49 (PETXN0)
unnamed: C157.1, U8.52 (PETXN1)
unnamed: C159.1, U8.48 (PETXP0)
unnamed: C160.1, U8.51 (PETXP1)
unnamed: R24.1, U8.67 (REXT)
unnamed: R96.1, U8.23 (TESTEN)
unnamed: R92.1, U8.18 (UART_RX)
unnamed: R65.1, U8.17 (UART_TX)
unnamed: C205.1, U8.69 (XI), Y2.3
unnamed: C204.2, U8.70 (XO), Y2.1
unnamed: R71.1, R74.2, U9.4 (FB)
unnamed: U8.86 (SPI_CLK), U11.6 (CLK)
unnamed: R190.1, U11.5 (DI(IO0))
unnamed: R190.2, U8.87 (SPI_DIO), U11.2 (DO(IO1))
unnamed: U8.88 (SPI_CS), U11.1 (~CS)
unnamed: R106.1, R107.2, U12.4 (ADJ)
unnamed: R101.2, U14.9 (CFG1)
unnamed: R48.2, U14.8 (VBUS)
unnamed: C66.1, R50.2, U14.1 (VHV)
unnamed: C70.2, U15.1 (BOOST)
unnamed: C72.2, R57.1, R58.2, U15.3 (FB)
unnamed: C70.1, L1.1, U15.6 (SW)
unnamed: C71.2, U16.1 (BOOST)
unnamed: C73.2, R59.1, R60.2, U16.3 (FB)
unnamed: C71.1, L2.1, U16.6 (SW)
unnamed: R82.2, U79.6 (CLK)
unnamed: R83.2, U79.5 (DI(IO0))
unnamed: R84.2, U79.2 (DO(IO1))
unnamed: R85.2, U79.3 (IO2)
unnamed: R86.2, U79.7 (IO3)
unnamed: R80.2, R81.2, U79.1 (~CS)
VCC25O: C165.2, U8.57 (VCC25O)
VDC: A1.250 (VIN), A1.251 (VIN), A1.252 (VIN), A1.253 (VIN), A1.254 (VIN), A1.255 (VIN), A1.256 (VIN), A1.257 (VIN), A1.258 (VIN), A1.259 (VIN), A1.260 (VIN)
sic-gnd: C1.2, C2.2, C125.2, C149.2, IC2.3 (PGND_1), IC2.4 (PGND_2), IC2.13 (PGND_3), IC2.16 (AGND_1), IC2.25 (AGND_2), IC2.27 (PGND_4), IC2.29 (PGND_5), R26.1, R39.1

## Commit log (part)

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2025-08-31 Add initial files
2025-08-31 switch to 5v power plane
2025-08-31 add crystal for rp2040 and update readme
2025-09-01 switch to 20V PD input
2025-09-04 replace the 12v buck with a 12 amp capable buck
    also removed soft start circuit because its built in the Buck Converter IC
2025-09-23 Add step down converter
    Prevent 20v going into the lattepanda mu, it has been stepped down to 15v
2026-02-12 Major Overhaul
2026-02-12 Relocate 1v0 PMIC
2026-02-12 Fix Ground Plane Intteruptions
2026-02-12 Fix Further Ground Plane Intteruptions
2026-06-03 Update Board According to DFA Review
    Updated Ethernet Jack
    Updated L3 Inductor
    Fixed a few errors
    Updated mounting hole size
2026-06-06 further changes required by DFA review
2026-06-10 Further DFA Changes
    Changed RJ45 jack to one capable of 10gbps, to remove any possible bottleneck
2026-06-10 remove unused component schematics
2026-06-10 Update PCB Photos
2026-06-10 add another PCB Photo
2026-06-12 Add board status to ReadME
2026-06-12 Update some information on the board
